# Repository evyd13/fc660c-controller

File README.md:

# FC660C Controller with USB-C

## Features
- Fully compatible with keymaps for Hasu's FC660C controller
- USB-C port (required small case modification)
- ESD protection circuit

## Bill of materials (BOM)
Please have a look at the production files!

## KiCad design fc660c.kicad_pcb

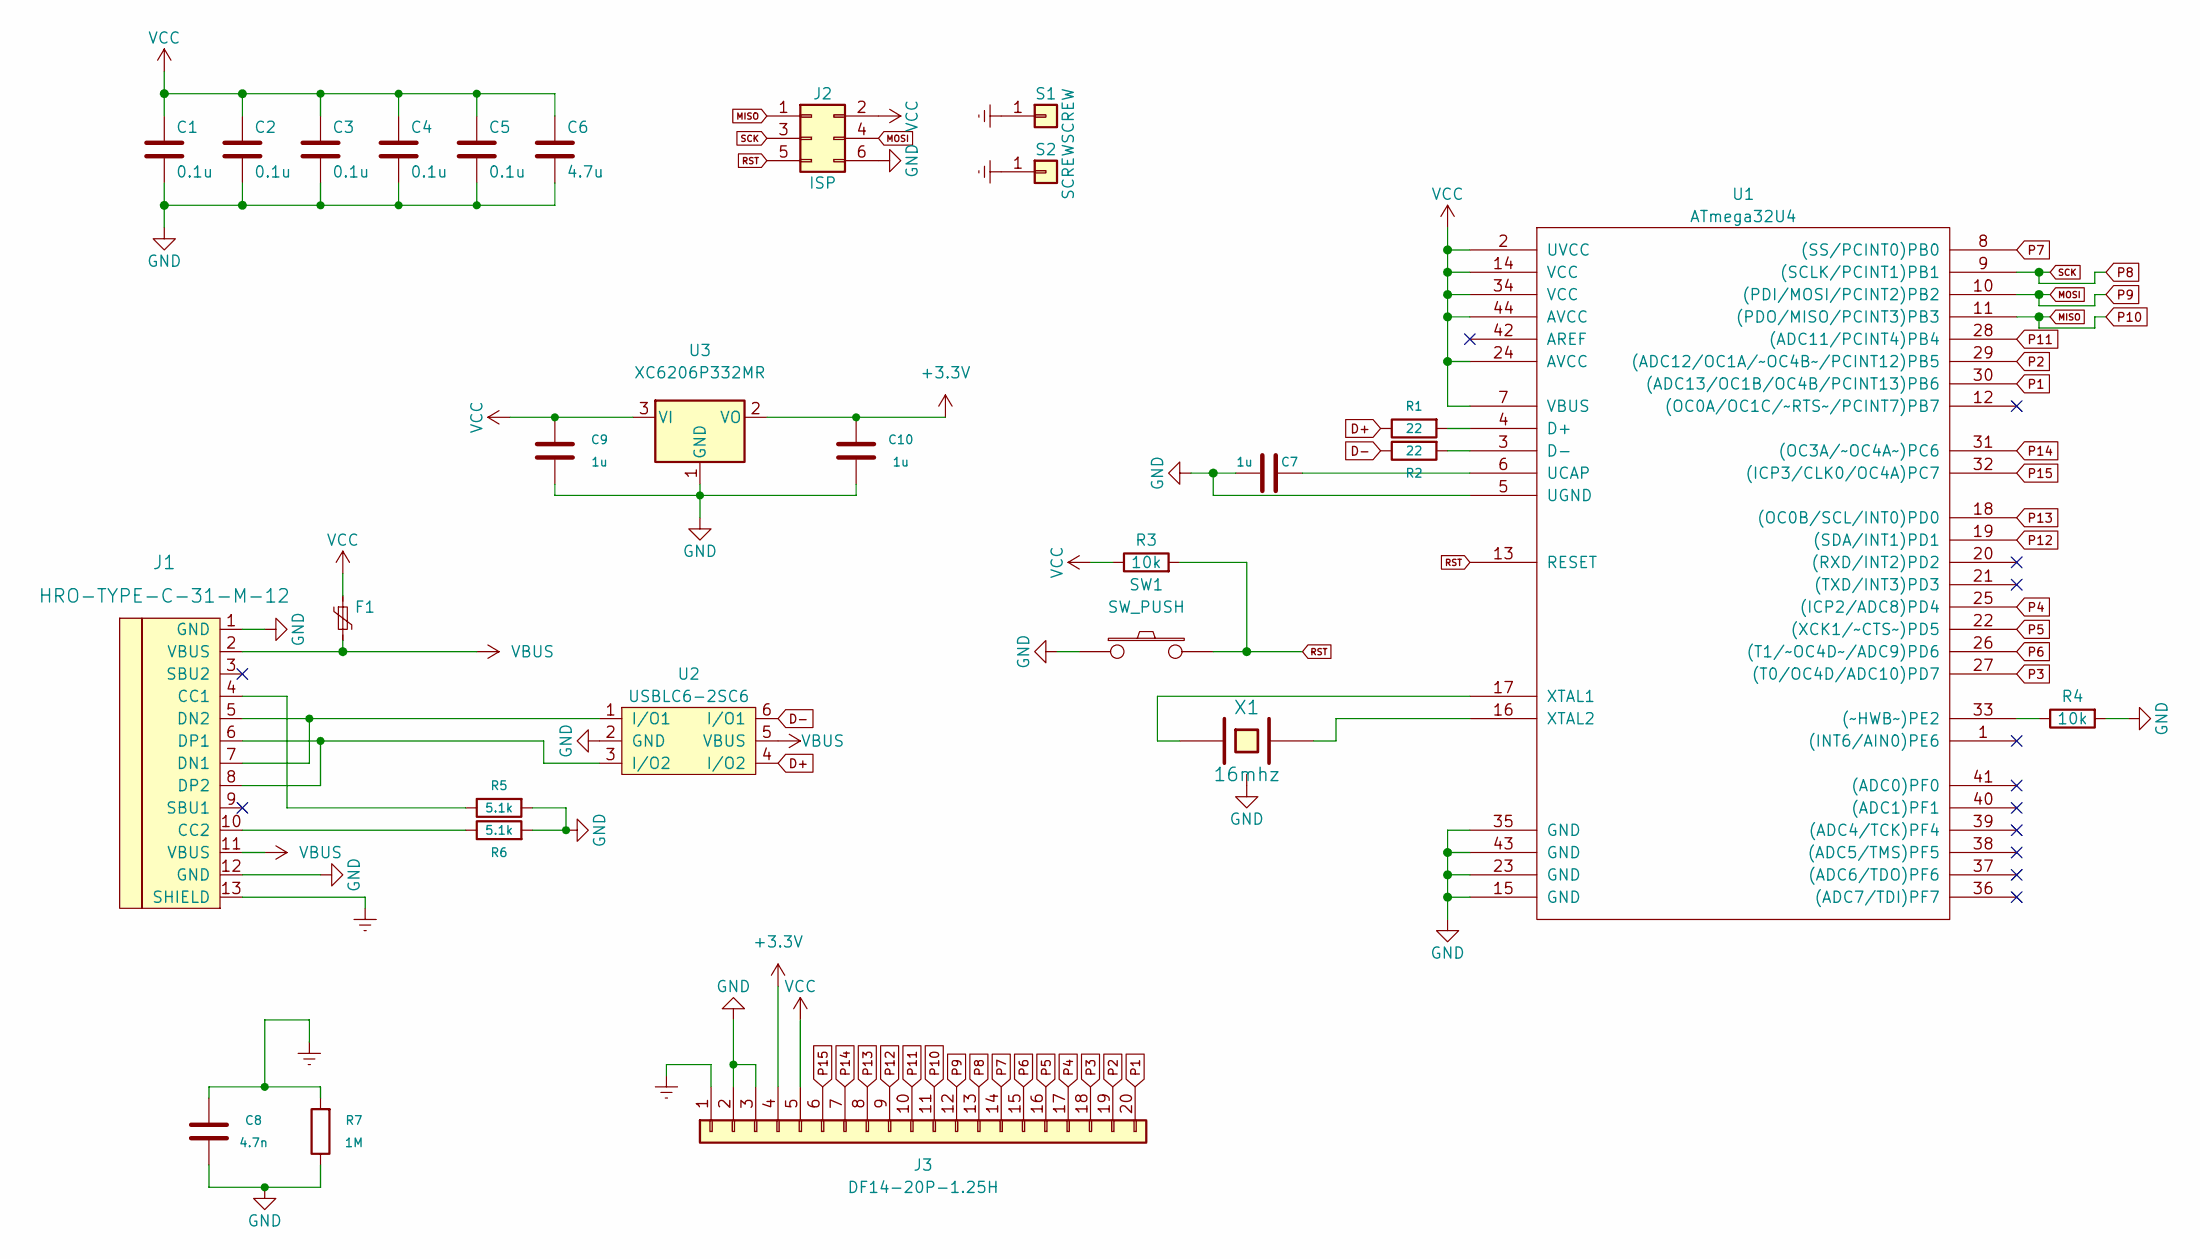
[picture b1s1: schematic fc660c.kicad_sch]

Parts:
C1, C2, C3, C4, C5: 0.1u; C_0805
C6: 4.7u; C_0805
C7, C9, C10: 1u; C_0805
C8: 4.7n; C_0805
F1: Polyfuse_Small; F_0805
J1: HRO-TYPE-C-31-M-12
J2: ISP; isp_standard
J3: DF14-20P-1.25H
R1, R2: 22; R_0805
R3, R4: 10k; R_0805
R5, R6: 5.1k; R_0805
R7: 1M; R_0805
S1, S2: SCREW; screw
SW1: SW_PUSH; SW_SPST_TL3342
U1: ATmega32U4; ATMEGA32U4
U2: USBLC6-2SC6
U3: XC6206P332MR; SOT-23
X1: 16mhz; Resonator_SMD_muRata_CSTNExxV-3Pin-p1.2

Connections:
+3V3: C10.1, J3.4, U3.2 (VO)
D+: R1.1, U2.4 (I/O2)
D-: R2.1, U2.6 (I/O1)
Earth: C8.1, J1.13 (SHIELD), J3.1, R7.2, S1.1, S2.1
GND: C1.2, C2.2, C3.2, C4.2, C5.2, C6.2, C7.2, C8.2, C9.2, C10.2, J1.1 (GND), J1.12 (GND), J2.6, J3.2, J3.3, R4.2, R5.2, R6.2, R7.1, SW1.1, U1.5 (UGND), U1.15 (GND), U1.23 (GND), U1.35 (GND), U1.43 (GND), U2.2 (GND), U3.1 (GND), X1.3
MISO: J2.1, J3.11, U1.11 ((PDO/MISO/PCINT3)PB3)
MOSI: J2.4, J3.12, U1.10 ((PDI/MOSI/PCINT2)PB2)
unnamed: C7.1, U1.6 (UCAP)
unnamed: J1.4 (CC1), R5.1
unnamed: J1.5 (DN2), J1.7 (DN1), U2.1 (I/O1)
unnamed: J1.6 (DP1), J1.8 (DP2), U2.3 (I/O2)
unnamed: J1.10 (CC2), R6.1
unnamed: R1.2, U1.4 (D+)
unnamed: R2.2, U1.3 (D-)
unnamed: R4.1, U1.33 ((~HWB~)PE2)
unnamed: U1.16 (XTAL2), X1.2
unnamed: U1.17 (XTAL1), X1.1
P1: J3.20, U1.30 ((ADC13/OC1B/OC4B/PCINT13)PB6)
P2: J3.19, U1.29 ((ADC12/OC1A/~OC4B~/PCINT12)PB5)
P3: J3.18, U1.27 ((T0/OC4D/ADC10)PD7)
P4: J3.17, U1.25 ((ICP2/ADC8)PD4)
P5: J3.16, U1.22 ((XCK1/~CTS~)PD5)
P6: J3.15, U1.26 ((T1/~OC4D~/ADC9)PD6)
P7: J3.14, U1.8 ((SS/PCINT0)PB0)
P8: J2.3, J3.13, U1.9 ((SCLK/PCINT1)PB1)
P11: J3.10, U1.28 ((ADC11/PCINT4)PB4)
P12: J3.9, U1.19 ((SDA/INT1)PD1)
P13: J3.8, U1.18 ((OC0B/SCL/INT0)PD0)
P14: J3.7, U1.31 ((OC3A/~OC4A~)PC6)
P15: J3.6, U1.32 ((ICP3/CLK0/OC4A)PC7)
RST: J2.5, R3.2, SW1.2, U1.13 (RESET)
VBUS: F1.2, J1.2 (VBUS), J1.11 (VBUS), U2.5 (VBUS)
VCC: C1.1, C2.1, C3.1, C4.1, C5.1, C6.1, C9.1, F1.1, J2.2, J3.5, R3.1, U1.2 (UVCC), U1.7 (VBUS), U1.14 (VCC), U1.24 (AVCC), U1.34 (VCC), U1.44 (AVCC), U3.3 (VI)

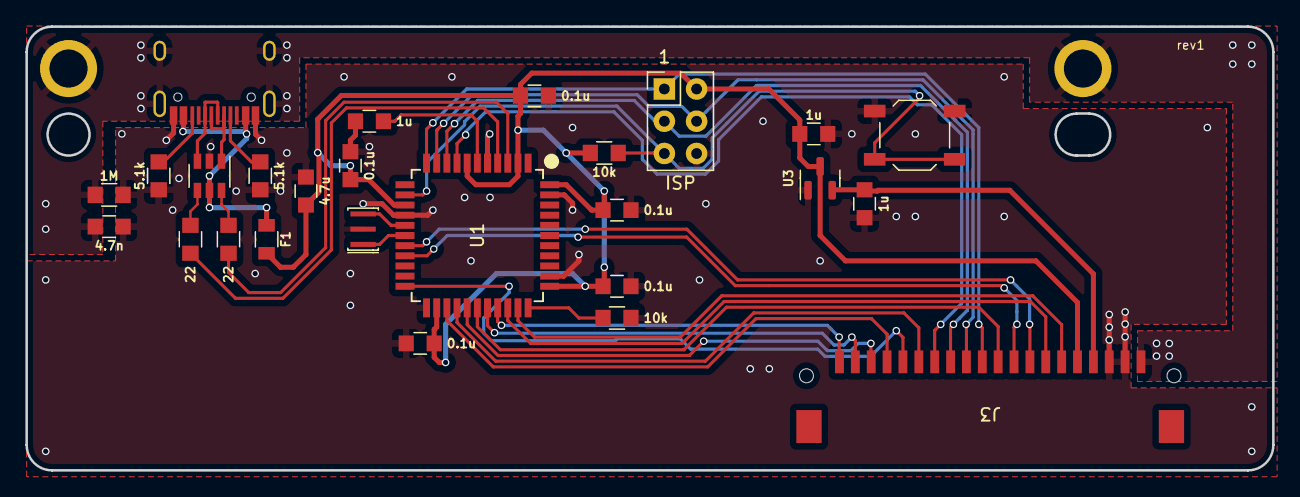
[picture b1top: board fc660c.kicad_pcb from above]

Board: 2 copper layers, 98.2 x 35.0 mm, 28 parts (0 on the bottom side), 33 nets.

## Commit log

2021-12-17 Upload rev1 files
2021-12-31 Add license
